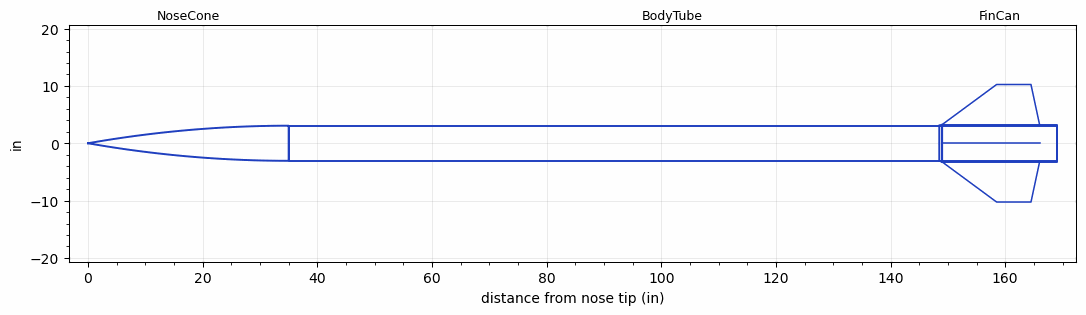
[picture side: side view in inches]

<RASAeroDocument>
 <FileVersion>2</FileVersion>
 <RocketDesign>
  <NoseCone>
   <Length>35</Length>
   <Diameter>6.125</Diameter>
   <Shape>Tangent Ogive</Shape>
   <BluntRadius>0.03</BluntRadius>
   <Location>0</Location>
  </NoseCone>
  <BodyTube>
   <Length>134</Length>
   <Diameter>6.125</Diameter>
   <Location>35</Location>
  </BodyTube>
  <FinCan>
   <Length>20</Length>
   <Diameter>6.5</Diameter>
   <InsideDiameter>6.125</InsideDiameter>
   <RailGuideDiameter>0.75</RailGuideDiameter>
   <RailGuideHeight>0.75</RailGuideHeight>
   <Location>169</Location>
   <ShoulderLength>0.5</ShoulderLength>
   <Offset>-20</Offset>
   <Fin>
    <Count>4</Count>
    <Chord>17</Chord>
    <Span>7</Span>
    <SweepDistance>9.5</SweepDistance>
    <TipChord>6</TipChord>
    <Thickness>0.25</Thickness>
    <LERadius>0.015</LERadius>
    <Location>20</Location>
    <AirfoilSection>Hexagonal</AirfoilSection>
    <FX1>0.125</FX1>
    <FX3>0.125</FX3>
   </Fin>
  </FinCan>
  <Surface>Smooth Paint</Surface>
  <ModifiedBarrowman>True</ModifiedBarrowman>
  <Turbulence>True</Turbulence>
  <SustainerNozzle>3.09</SustainerNozzle>
  <UseBooster1>False</UseBooster1>
  <UseBooster2>False</UseBooster2>
  <Comments>A-601 Rocket
P4935 Loki-EX Motor
Ray Kinsel

GPS Altitude = 42771 ft
Adept Barometric Altitude = 42231 ft
ARTS II Barometric Altitude = 40113 ft
ARTS II Integrated Accelerometer Altitude = 44924 ft

Final Altitude - GPS Altitude - 42771 ft

RASAero II Prediction = 41098 ft
Error = -3.91%
</Comments>
 </RocketDesign>
 <LaunchSite>
  <Altitude>3933</Altitude>
  <Pressure>0</Pressure>
  <RodAngle>0</RodAngle>
  <RodLength>14</RodLength>
  <Temperature>80</Temperature>
  <WindSpeed>0</WindSpeed>
 </LaunchSite>
 <Recovery>
  <Altitude1>1000</Altitude1>
  <Altitude2>1200</Altitude2>
  <DeviceType1>Parachute</DeviceType1>
  <DeviceType2>Parachute</DeviceType2>
  <Event1>True</Event1>
  <Event2>True</Event2>
  <Size1>96</Size1>
  <Size2>160</Size2>
  <EventType1>Apogee</EventType1>
  <EventType2>Altitude</EventType2>
  <CD1>1.33</CD1>
  <CD2>1.33</CD2>
 </Recovery>
 <SimulationList>
  <Simulation>
   <SustainerEngine>P4935  (LR-EX)</SustainerEngine>
   <SustainerLaunchWt>154.46</SustainerLaunchWt>
   <SustainerNozzleDiameter>3.09</SustainerNozzleDiameter>
   <SustainerCG>113.2</SustainerCG>
   <SustainerIgnitionDelay>0</SustainerIgnitionDelay>
   <Booster1SeparationDelay>0</Booster1SeparationDelay>
   <Booster1IgnitionDelay>0</Booster1IgnitionDelay>
   <IncludeBooster1>False</IncludeBooster1>
   <Booster2Delay>0</Booster2Delay>
   <IncludeBooster2>False</IncludeBooster2>
   <TimetoApogee>49.08777</TimetoApogee>
   <MaxAltitude>41097.7</MaxAltitude>
   <MaxVelocity>2088.743</MaxVelocity>
  </Simulation>
 </SimulationList>
</RASAeroDocument>
